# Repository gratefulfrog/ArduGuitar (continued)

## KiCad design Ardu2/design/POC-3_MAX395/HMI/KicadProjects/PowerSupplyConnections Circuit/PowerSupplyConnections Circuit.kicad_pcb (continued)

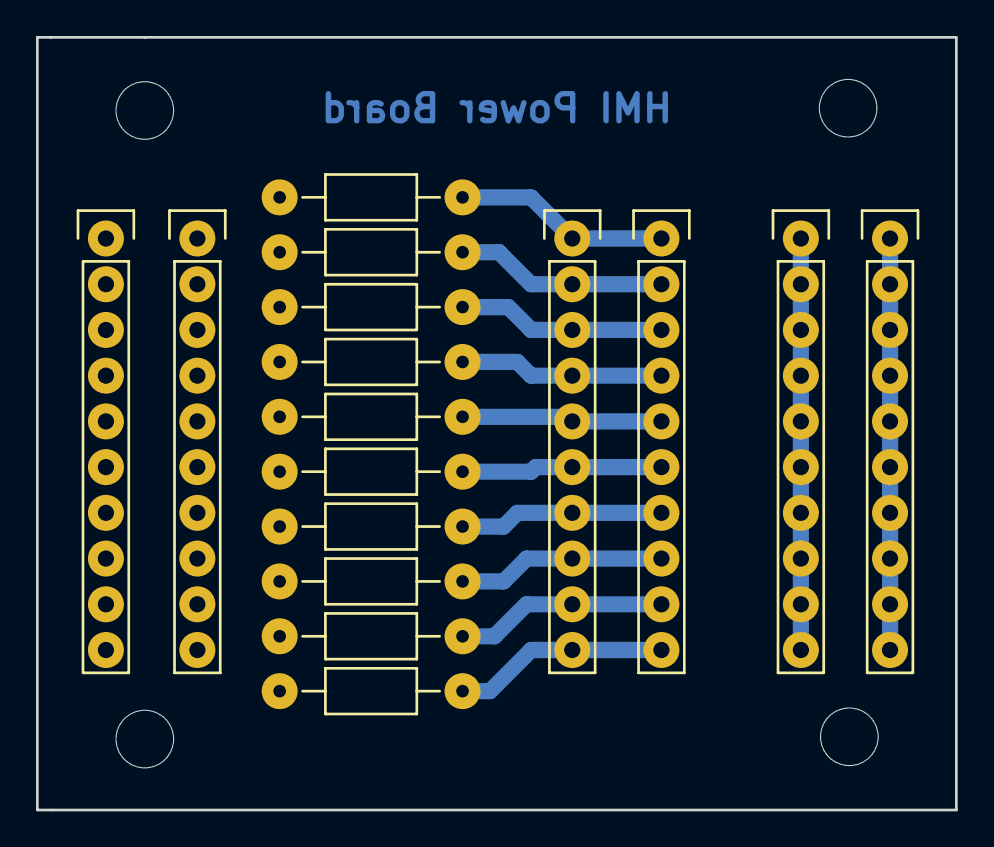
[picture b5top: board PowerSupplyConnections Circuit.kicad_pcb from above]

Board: 2 copper layers, 51.1 x 42.9 mm, 16 parts (0 on the bottom side), 13 nets.

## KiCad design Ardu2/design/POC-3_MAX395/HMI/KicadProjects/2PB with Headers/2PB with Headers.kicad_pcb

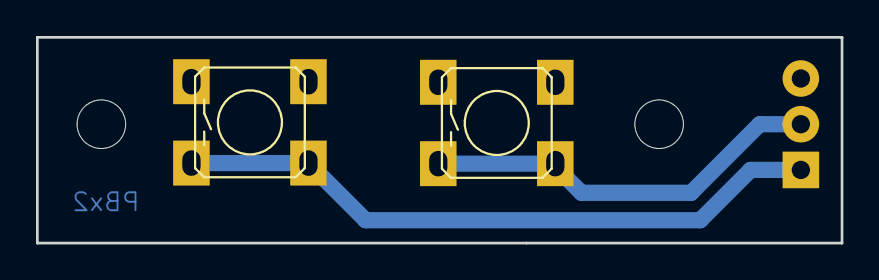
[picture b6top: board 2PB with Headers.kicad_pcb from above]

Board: 2 copper layers, 44.7 x 11.4 mm, 3 parts (1 on the bottom side), 3 nets.

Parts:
GND P2 P1: CONN_01X03; Pin_Header_Straight_1x03
SW1, SW2: SW_PUSH; AB2_PB_MOM_6MM_PTH_BLK

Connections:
GND: GND P2 P1.3, SW1.1, SW2.1
unnamed: GND P2 P1.1, SW1.2
unnamed: GND P2 P1.2, SW2.2

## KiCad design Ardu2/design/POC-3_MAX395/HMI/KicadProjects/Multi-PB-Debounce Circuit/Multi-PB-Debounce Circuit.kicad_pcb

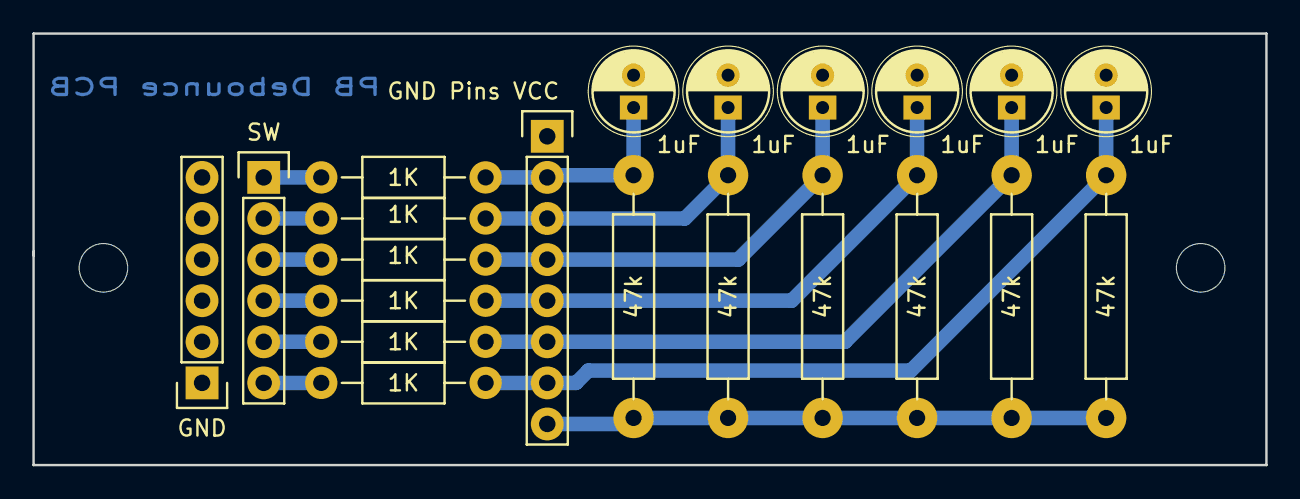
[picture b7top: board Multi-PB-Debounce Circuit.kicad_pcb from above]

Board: 2 copper layers, 76.2 x 26.7 mm, 21 parts (0 on the bottom side), 14 nets.

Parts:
C1, C2, C3, C4, C5, C6: 1uF; C_Radial_D5_L11_P2
GND: CONN_01X06; Pin_Header_Straight_1x06
GND Pins VCC: CONN_01X08; Pin_Header_Straight_1x08
R1, R2, R5, R7, R9, R11: 1K; Resistor_Horizontal_RM10mm
R3, R4, R6, R8, R10, R12: 47k; Resistor_Horizontal_RM15mm
SW: CONN_01X06; Pin_Header_Straight_1x06

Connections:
/Pin0: C2.1, GND Pins VCC.2, R1.1, R4.2
/Pin1: C3.1, GND Pins VCC.3, R5.1, R6.2
/Pin2: C4.1, GND Pins VCC.4, R7.1, R8.2
/Pin3: C5.1, GND Pins VCC.5, R9.1, R10.2
/Pin4: C6.1, GND Pins VCC.6, R11.1, R12.2
/Pin5: C1.1, GND Pins VCC.7, R2.1, R3.2
/SW0: R1.2, SW.1
/SW1: R5.2, SW.2
/SW2: R7.2, SW.3
/SW3: R9.2, SW.4
/SW4: R11.2, SW.5
/SW5: R2.2, SW.6
GND: C1.2, C2.2, C3.2, C4.2, C5.2, C6.2, GND.1, GND.2, GND.3, GND.4, GND.5, GND.6, GND Pins VCC.1
VCC: GND Pins VCC.8, R3.1, R4.1, R6.1, R8.1, R10.1, R12.1

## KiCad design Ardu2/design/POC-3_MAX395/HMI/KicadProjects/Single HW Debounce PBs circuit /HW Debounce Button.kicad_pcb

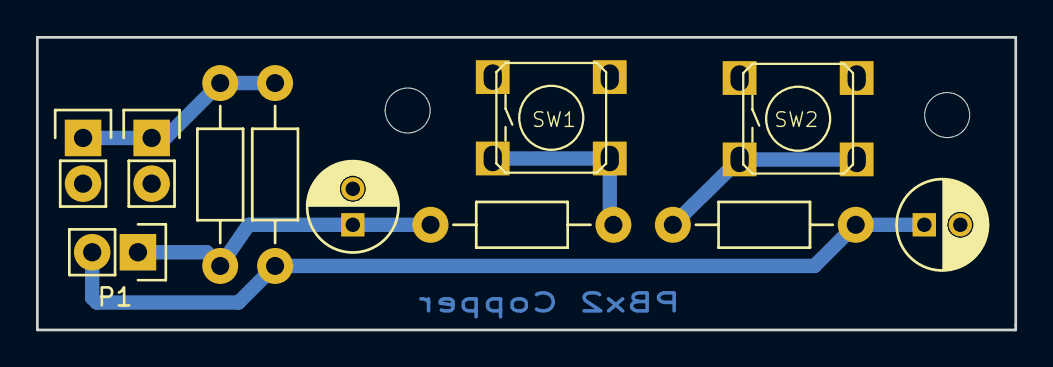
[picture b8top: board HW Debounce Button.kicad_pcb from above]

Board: 2 copper layers, 54.4 x 16.3 mm, 11 parts (0 on the bottom side), 6 nets.

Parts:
C1, C2: 1uF; C_Radial_D5_L11_P2
P1, P2, P3: CONN_01X02; Pin_Header_Straight_1x02
R1, R2: 1K; Resistor_Horizontal_RM10mm
R3, R4: 47k; Resistor_Horizontal_RM10mm
SW1, SW2: SW_PUSH; AB2_PB_MOM_6MM_PTH_BLK

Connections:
/Pin1: C1.1, P1.1, R2.1, R3.2
/Pin2: C2.1, P1.2, R1.1, R4.2
GND: C1.2, C2.2, P2.2, P3.2, SW1.1, SW2.1
unnamed: R1.2, SW2.2
unnamed: R2.2, SW1.2
VCC: P2.1, P3.1, R3.1, R4.1

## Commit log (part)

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2015-01-12 new 4316 inverter-vol-tone schematic
2015-01-13 PCB for Inverter-Vol-Tone Switchboard
2015-01-13 designed PCB for Inverter-Vol_Tone, corrected schematic as well
2015-01-16 master tone PCB
2015-02-12 All IVT SPDT PCBs complete
2015-02-12 IVT Switchboards and Breadboards assembled
2015-03-01 pyboard start spi
2015-03-01 cleaned up directories
2015-03-01 Daisy chained shift regs on pyboard
2015-03-01 fixed erroneous comments
2015-03-08 master tone vol MAX395 ok
2015-03-10 MAX395 Switch Array Schematic
2015-03-18 some initial python work
2015-03-19 working on the pyboard code
2015-03-22 update to component model
2015-03-22 update to component classes
2015-03-22 closer and closer to a first implementation
2015-03-24 continued work on components and app - still some issues with conflicts of interest
2015-03-24 looks like we have the system ready just need to send the bits
2015-03-26 updates for compatability with python3.4.0 as on the pyboard as well as consistencey and documentation updates
2015-03-26 working and documented-tested on-board and in python3.4.0
2015-03-27 added references to micropython SPI documentation
2015-03-27 minor updates to enable better debuggging during tests
2015-03-29 fixed issues with eval on pyboard - workaround is not nice but allows for loading of configs
2015-03-29 test class to see why eval & exec fail on micropython
2015-04-03 update to 4316c Master VT schematic following discovery of error
2015-04-04 updated MAX395 schemtatics tone resistor values
2015-04-08 First FULLY working verison of thecircuit
2015-04-08 conformed schemtatics and dictMgr configs to experimental results
2015-04-13 more work on the circuit and the 10PDT mount
2015-04-13 update to the 10PDT mount
2015-04-18 no significant change only cosmetics
2015-04-30 create softX method in app for make before break implementation
2015-05-02 vactrol control attempts at eliminating pop all failed
2015-05-03 Vactrol shunt schematic added
2015-05-04 initial work on PCBs
2015-05-04 finished IVT PCB b
2015-05-04 new version C of the IVT PCB
2015-05-06 4316d IVT PCBe seems Good To Go
2015-05-06 results of shunt tests
2015-05-07 Overview for MAX395 implementation
2015-05-07 working on MAX395 layout
2015-05-08 update to the board connection overview still needs work
2015-05-09 more updates to the MAX395 overview
2015-05-19 work on pcb, really hard
2015-05-19 still more work on pcb, really REALLY hard
2015-05-21 trying to make the pcb layouts, so so hard...
2015-05-22 update to MAX395 MVT Audio schematic version e
2015-05-24 initial Kicad schematic of full circuit
2015-05-24 first full KICAD schematic
2015-05-25 progress on kicad design
2015-05-28 ùore pcb kicad work, mostly failures
2015-05-28 more pcb experiments
2015-05-29 looking better and better
2015-05-30 seems pretty good, again...
2015-05-31 updates after testing on breadboard - still need reverse polarity protection
2015-05-31 reverse polarity added, Cout+ net corrected
2015-06-02 MVT breadboard ready for test
2015-06-04 MVT breadboard test SUCCESS
2015-06-09 First tests and first success with the MAX395 breadboards including shunt
2015-06-09 fixing git error
2015-06-10 minor improvements to PCB
2015-06-11 connection tester added
2015-06-11 Updates after mockup of PCB
2015-06-11 Preparing GERBER generation
2015-06-15 updates after circuit review with SENSEI
2015-06-15 tweaked PCB tracks, added labels
2015-06-17 updates to the headers conf on pcb
2015-06-20 updates to selector switch class
2015-06-24 minor updates
2015-07-03 hardware implementation and some restructuring
2015-07-03 hardware restructuring
2015-07-04 accelerometer tested and operated succesfully
2015-07-04 updates to acc.py now stable
2015-07-10 creation of outils.py and the RMap class to map from one range of values to another
2015-07-10 creation of VoltageDividerPot in hardware.py
2015-09-12 updates to PCB for EuroCircuits Fab
2015-09-21 updated PCB image to conform to design
2015-09-27 ps2 arduino code from internet
2015-09-27 arduino code for ps2 trackball
2015-09-27 playing around with PS2Tester.py
2015-09-27 playing around still with PS2Tester.py
2015-10-02 more ps2 tests
2015-10-05 more ps2 trials with no succes
2015-10-09 update to ps2 python class, addition of test execution file
2015-10-10 still more ps2 failure
2015-10-11 attempts to use native code emmitter
2015-10-19 new ps2 attempt underwork
2015-10-23 first working ps2 driver for the pyboard
2015-10-26 added 4 pin version of PS2 in python
2015-10-26 a near working version of the ps2 in is1.py - still need to make it good
2015-10-27 first fully function ps2 implementation in micropython
2015-10-27 ps2 interrupt version ok, but still has timing issues... that's enough
2015-10-28 updated ps2 interrupt version with a timeout to avoid hanging
2015-11-04 updates to the pcb layout this corresponds to the working prototype PCB
2015-11-04 lcd experiments ok
2015-11-05 work on the HMI
2015-11-07 first HMI mock-up
2015-11-08 updates to HMI, v03
2015-11-09 HMI prototype cut files ready
2015-11-12 preliminary work on LED PCB
2015-11-14 more HMI circuit design
2015-11-18 HMI LED PCB 00
2015-11-18 HMI PCB v2a
2015-11-20 some photos added
2015-11-21 HMI PCB tested and working
2015-12-09 removed unused variable
2015-12-13 New test code for interrupt driven input on tactile switches and 5-position seletors
2015-12-18 tried to use flags to get the itnerrupts to work with bounce, failed
2015-12-19 more debouncing, almost works now
2016-01-05 more hw debouncing, seems a bit better
2016-01-06 new HMI cutout for stnd button spacing
2016-01-24 working on debounce hmi pcb and panel
2016-01-25 muli PB PCB work
2016-01-27 PB PCB work
2016-04-01 dbh6 ran on 6 pushbutton PCBs + HW deounce PCB - worked perfectly!
2016-04-04 updated the HMI cut file for pb pcbs
2016-04-10 added q based interrupt handler test file
2016-04-10 added q based interrupt handler test file updated
2016-04-13 interrupt driven event loop testing
2016-04-18 typo correction
2016-04-27 LCD Mgr operational
2016-05-02 tested processing python mode with the LCDMgr and it works
2016-05-03 initialize
2016-05-03 test update
2016-05-03 this still fails
2016-05-03 this may work
2016-05-03 more tests of io webpages
2016-05-04 added function pointer tests
2016-05-04 trying still
2016-05-04 giving up on web stuff for now
2016-05-04 converting HMI simulator to python
2016-05-06 updating the python HMI
2016-05-07 added doc link to index
2016-05-10 made the selector work
2016-05-10 some trackball sim work
2016-05-11 still more trackball work
2016-05-12 trackball updates, processing-python code is broken
2016-05-12 trackball integrated, but in processing 3.0.2 only
2016-05-12 SplitPotTester operatinal!
2016-05-13 refined HMI Mockup to make it closer to the real thing
2016-05-13 implemented control exclusion
2016-05-13 update to canvas dimensions
2016-05-15 started working on encode/decode for queueing
2016-05-18 more q integration
2016-05-18 only the trackball q processing remains to be integrated
2016-05-19 TrackBall integrated in HMI - HMI now fully integrated version 0
2016-05-19 separated pollables and interruptables in event loop
2016-05-20 updated to load configs from presets
2016-05-22 added an image and improved the tracing
2016-05-23 working on presets
2016-05-26 PyHMI is now complete. Next step: communicate with the pyboard
2016-05-26 ported the parse.lisp file to python3
2016-05-29 corrected errors and finalized connection inversion parsing
2016-05-29 improved order of symbols in LCD editor
2016-05-30 First integrated version of emulator with comms to the pyboard!
2016-06-01 final version pf power distribution board pcb
2016-06-03 working on the HMI LEDs
2016-06-06 beginning of the HMI integration with the pyboard code
2016-06-08 implmented tracking style split pots, reverted pyboard firmware
2016-06-10 reorginized directories
2016-06-11 integrated physical LCD
2016-06-11 ported Q and EnQueueable
2016-06-12 PB and LCD fully integrated. Q processing started.
2016-06-14 added my own version of a csv.py, seems ok, needs more tests...
2016-06-15 more porting... recursion & memory problems...
2016-08-12 some cosmetic updates
2016-08-16 created Tools directory, some tools moved there, a pathSet function to allow for sd card priority importing
2016-08-25 created Makefile for byte compliation and firmware deployment
2016-08-25 fixed defect in the csv parsing, more checking still needed for default preset creation
2016-08-26 NOW RUNS, but pb with interrupts on selector, added ljust function to outils.py
2016-08-26 Working byte compiled version with SelectorInterrupt integrated
2016-08-26 ported hradware.TrackBall, updated q to increase the qLen and try to avoid overload due to high trackabll spinning
2016-08-27 sd-card testing framework and initial work on SplitPot inDraftDevt, some other minor updates
2016-08-29 DraftDevt SplitPot.py FINALLY now works in both track and no track mode
2016-08-29 updated state and splitPot to allow tweaking, tested use of static whoFuncs for app.pb method still tb programmed
2016-08-31 found dictionary bug, wrote workaround, and we now have a FULLY FUNCTIONAL SYSTEM
2016-09-01 worked on demonstrating the frozen string issue
2016-09-02 working towards integration of hardware.TremVib but not quite there yet
2016-09-03 issue with ExtInt on pins X9 and X10 and Accel object explored and reported
2016-09-04 Update Readme after V0.99 tag
2016-09-09 working on the sequencer
2016-09-12 implemented sequencing, fully
2016-10-06 updates do get the pb LEDs working
2016-10-06 update the frozen code makefile to take into account changes in myp-cross
2016-10-07 updates to fix what's broken, new MicroValuator class in test
2016-10-24 created a new peripherals PCB
2016-10-26 updated to HMI PCB after SENSEI review
2016-10-28 updated to HMI PCB after second SENSEI review
2016-11-12 preared HMI-PCB front silk layer for soldering
2016-11-12 more work on HMI PCB
2016-11-14 working on HMI
2016-11-15 working on PyGuitar HMI
2016-12-24 seems like a working version with full PCB integraton
2016-12-25 updates to save edited conf as preset but not to disk
2016-12-29 debugging the q problem
2016-12-30 correcting sw defects - still 1 to go
2016-12-31 minor update to set default tone range to 5 everywhere
2016-12-31 thoughts about split pot tracking
2017-01-01 update to include working SplitPot tracking mode
2017-01-05 added schematics for std and reverse pot volume wiring
2017-01-06 guitar wiring schematic
2017-01-08 fixed upper no parenthesis call in sParse
2017-01-14 updated guitar wiring
2017-02-22 some minor updates
2017-05-24 working on mounting block design
2017-06-04 udpate mounting block design
2017-06-06 progress on mounting blocks for HMI
2017-06-06 created drilling jig for spacer cylinders
2017-06-06 drilling jigs continued
2017-06-09 more work on 3D printed parts for HMI
2018-01-03 some ardu3 concept stuff
2018-01-03 oled sim stuff
2018-01-03 trying to get oled sim to work
2018-01-03 cleaned up
2018-01-03 continued oled sim
2018-02-05 added oled test
2018-02-07 draft devt.
2018-02-08 created tester for the AD75019
2018-02-09 working on the AD75091
2018-02-12 AD75091 arduino code - failure
2018-02-13 AD75019 tests
2018-02-15 added some AD75019 scope images
2018-02-17 added some more AD75019 test results
2018-02-22 created library for Adafruit joystick 512
2018-04-19 more updating to test AD75019
2018-05-06 draft schematic for unity gain vol tone
2018-05-09 working on draft AD75019 test code
2018-05-11 preparing test code for Mega driver to run Yannicks Matrix board
2018-05-13 AD75019 Gui tester work
2018-05-13 AD75019 gui progress - comms and automation work
2018-05-14 gui work for AD75019 tester
2018-05-14 only the matrix remains for AD75019 tester
2018-05-14 still closer to the matrix for AD75019 tester
2018-05-15 gui defect repair
2018-05-15 gui cosmetics
2018-05-16 reduced spi rate to 500khz made no difference
2018-05-19 preparing to test the Maxim digipots
2018-05-29 preparing for AD75019 sine wave test
2018-05-29 finally go the AD75019 to work with 12v and an analog sine wave
2018-05-31 work towards pyboard version of AD75019 tester
2018-05-31 ad75019SPIMgr.py operational
